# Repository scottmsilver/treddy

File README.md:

# Treddy

> A 2005 treadmill that listens when you talk to it.

A Raspberry Pi sits between the console and motor controller of a Precor 9.31 treadmill, intercepting the serial bus. It runs an AI coach (Gemini), voice control, a tablet UI, and a Bluetooth daemon that makes Zwift think it's a modern smart treadmill.

---

## Voice + AI Coach

- "Set speed to 5" or "give me a 20-minute hill workout" — Gemini controls the belt directly
- Voice works mid-run via Gemini Live (real-time, no wake word)
- Says "this is the hardest interval" or "you're faster than last time" because it can query your run history

## Apps

- **Android** (Kotlin + Compose): runs on a tablet mounted on the treadmill console
- **Web** (React + TypeScript): same features, any browser
- Workout library, run history, live elevation profile, calorie tracking

## Bluetooth

- Rust daemon makes the treadmill show up in Zwift, Peloton, QZ Fitness, and Apple Watch as a standard FTMS device
- Fitness apps can read speed/incline and write speed/incline commands back

## Heart Rate

- Connects to any Bluetooth heart rate strap
- HR shows in the UI and feeds into calorie calculations

---

## Architecture

```
┌───────────────────────────┬───────────────────────────┐
│  Web UI (React + Vite)    │  Android (Kotlin+Compose) │
├───────────────────────────┴───────────────────────────┤
│  REST / WebSocket / Gemini Live (voice)               │
├───────────────────────────────────────────────────────┤
│  server.py (FastAPI)                                  │
│  Sessions, programs, AI chat, workout query DB        │
├──────────────────┬──────────────┬─────────────────────┤
│  treadmill_io    │  ftms-daemon │  hrm-daemon         │
│  C++20, GPIO     │  Rust, BLE   │  Rust, BLE          │
│  serial, safety  │  FTMS        │  heart rate         │
└──────────────────┴──────────────┴─────────────────────┘
                         │
                    Precor 9.31
                  RS-485 serial bus
```

- **C++ binary** — reads/writes the serial bus, enforces safety (3-hour timeout, physical buttons always override software)
- **Python server** — FastAPI. All the logic: Gemini AI, workouts, sessions, run history
- **FTMS daemon** — Rust. Bluetooth for fitness apps
- **HRM daemon** — Rust. Connects to heart rate straps
- **Web + Android** — display layers. All decisions happen server-side.

Details: [CLAUDE.md](CLAUDE.md)

---

## The Hardware Story

> The serial protocol turned out to be plain ASCII text. We just had the polarity wrong and spent days decoding "binary" that was actually `[key:value]` pairs with every bit flipped.

[Full reverse engineering writeup →](HARDWARE.md)

---

## Quick Start

**Prerequisites (Pi):** `libpigpio-dev`, `g++`, Python 3 with `google-genai`, `fastapi`, `uvicorn`, `gpxpy`. Gemini API key in `.gemini_key`.

```bash
make                         # build C++ binary
sudo ./build/treadmill_io    # start GPIO daemon (must be root)
python3 python/server.py     # start web server → https://<pi>:8000
```

**Deploy to Pi:**
```bash
make deploy    # stages, rsyncs, builds on Pi, restarts all 4 services
```

**Local dev (no Pi needed):**
```bash
TREADMILL_MOCK=1 ./scripts/dev.sh    # Caddy + server + Vite HMR
```

API reference, tests, and dev docs: [CLAUDE.md](CLAUDE.md)

## License

MIT

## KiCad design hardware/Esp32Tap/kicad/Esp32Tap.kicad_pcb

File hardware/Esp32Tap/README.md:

# Esp32Tap Rev E

**Status: HOLD.** Do not submit fabrication, authorize substitutions, pay, or
connect an Emulate-capable build to a treadmill until the applicable vendor,
firmware, harness, and bench gates are closed.

Esp32Tap sits inline between the console and motor-controller serial cables of
a Precor 9.31. In Proxy mode a normally closed relay preserves the passive
console path. Emulate mode transfers that path to a hardware-gated ESP32-S3
transmitter. The treadmill safety key remains authoritative; this board is not
a certified functional-safety controller.

## Rev E architecture

- J1/J2 are both the identical Molex 44144-0003 (441440003, LCSC C585890)
  right-angle SMD 8P8C RJ45 jack, placed by standard top-side reflow (no
  through-hole RJ45, no wave or manual solder step), edge-mounted with the
  mating opening facing off a short board edge: J1 (CONSOLE) off the left
  edge, J2 (MOTOR) off the right edge, so the board reads console → motor left
  to right. There is no pigtail harness and no mechanical keying between
  console and motor; CONSOLE/MOTOR silkscreen is the only differentiator. The
  ESP32 module is fully on-board (no antenna overhang, no carrier panel).
- The treadmill cable's +8 V rails are the only board power input and pass
  directly between J1/J2. F1/D1 protect only the local branch.
- USB-C is native data and VBUS-presence sensing only. USB cannot energize the
  board or relay; programming needs current-limited serial +8 V bench power.
- K1 needs three things at once: `TREAD_OK`, `RELAY_CMD` static high, and
  `RELAY_PULSE` (U1 IO8) toggling. `TREAD_OK` also gates the motor TX buffer.
  `RELAY_GATE` (U6 output to U5 enable and the Q1 base) is unchanged; Q3, in
  series with Q1's emitter, is fed only by a charge pump from `RELAY_PULSE`.
  Calculated, not measured: the relay releases roughly 50-150 ms after
  toggling stops (not a guaranteed deadline), and one stray edge cannot turn
  Q3 on. The switch alone is not single-fault tolerant (C22 short, R34 open,
  C23 open or Q3 drain-source short each defeat it; each needs a second fault). The pulse
  firmware is implemented in `firmware/esp32_rs` but unproven on hardware (bd
  `precor-9_3x-4uv` stays open until bench proof): a 500 µs `esp_timer`
  callback toggles IO8 (1 kHz) only while the WDT-supervised serial engine keeps
  renewing a permission (every 5 ms pass; it expires 20 ms after the last
  renewal), so a hung safety loop stops the pulses within 20 ms. It is
  deliberately not LEDC/RMT/hardware PWM. Pulses are wanted only in
  EntryWaitGap, EntryWaitFeedback, Emulating and ExitWaitGap, so in Proxy a
  stuck `RELAY_GATE` still cannot energize K1.
- K1 uses one transfer pole and one armature-feedback pole; feedback does not
  prove transfer-contact continuity.
- U3 (USBLC6-2SC6) pin 5 is unconnected. Tied to the VBUS sense net it let the
  ESP32 D+ pull-up leak onto that net and could assert `VBUS_PRESENT_N` with
  no cable.
- D5-D7 are Nexperia PESD5V0S1BA,115 (LCSC C19224), 5 V standoff, because the
  treadmill serial line voltage has never been measured.
- R33 (1 MΩ, `TREAD_OK` to `UV_SENSE`) adds about 0.5 V of undervoltage
  hysteresis. Nominal UV is about 5.9 V falling and 6.4 V rising
  (calculated and simulated).
- SW1/SW2 (Alps SKRPACE010) pad numbering was corrected to rows (pad 1 = both
  top lands, pad 2 = both bottom lands). The old column numbering would have
  shorted EN and IO0 to GND through the switch body. Not yet proven on
  hardware.
- Three board-only fiducials FID1-FID3, and all stock footprints pinned in
  `tools/footprint_sources/stock` (`MANIFEST.json` sha256) so a KiCad library
  update can no longer make the board unreproducible.

## Package map

| Path | Purpose |
|---|---|
| `tools/design.py` | Electrical source of truth |
| `kicad/Esp32Tap.kicad_sch` | Generated typed schematic |
| `kicad/Esp32Tap.kicad_pcb` | Generated 95 × 58 mm four-layer PCB |
| `bom/BOM.csv` / `bom/CPL-positions.csv` | Exact assembly inputs |
| `kicad/Esp32Tap-gerbers.zip` | Deterministic 13-member fabrication archive |
| `kicad/models/` | Committed RJ45 jack 3D model (STEP + WRL, LCSC C585890) |
| `sim/` | Eight ngspice decks (one retired) and dual-engine assertion runner |
| `firmware/PLAN.md` | Production firmware and bench contract |
| `firmware/safety_model.py` | Host reference, not flashable firmware |
| `ORDERING.md` | HOLD-state vendor review procedure |
| `AI-HANDOFF.md` | Concise continuation brief |

Do not repair generated hardware or assembly outputs by hand.

## Locked board facts

| Item | Rev E value |
|---|---|
| Finished outline | 95.0 × 58.0 mm |
| Stack | Four layers; modeled 1.59 mm `JLC04161H-7628` |
| Board connectors | J1/J2 both Molex 44144-0003 (`441440003`, LCSC C585890), right-angle SMD 8P8C RJ45, unkeyed, standard top-side reflow; J1 (CONSOLE) on the left short edge, J2 (MOTOR) on the right short edge |
| BOM | 82 line items, 46 distinct LCSC parts, about $8.79 parts per board (generated `bom/BOM.csv`) |
| DRC | Fresh KiCad 10.0.5, all severities and schematic parity: 0 violations. The earlier committed `drc.rpt` claimed 0 while 10.0.5 reported 8 |
| Antenna | U1 fully on-board; 3.25/3.30 mm body margins. Keepout split: inner and bottom layers forbid tracks, vias and fills; the front layer forbids fills and vias and allows the U1 pad fan-out stubs. Fixture keepout emitted 0.30 mm inset |
| USB | F.Cu-only, zero signal vias, 0.2906 mm width / 0.2000 mm controlled edge gap |
| USB paths | D− A/B 55.9528786214/54.9528786214 mm; D+ A/B 55.8729617233/54.8729617233 mm |
| USB per-side skew | 0.0799168981 mm |
| 2 A PCB trace-union drop | 84.929 mV supply plus return (+8 V 17.313 mΩ, explicit-copper GND 25.151 mΩ; layer-aware copper model) |
| +8 via maximum | 0.827864 A; 7.482581 °C rise |
| GND-via envelope | Full 2.0 A in any via; 12.273573 °C and 1.600310 mW at 20 µm plating |

The GND return result is a conservative trace-only solve. The independent
full-current GND-via envelope covers omitted plane sharing; neither result
claims complete installed behavior.

## Reproduce

From repository root:

```bash
make -C hardware/Esp32Tap clean-check
make -C hardware/Esp32Tap check
git diff --check
```

The simulation runner executes twelve decks three times on host ngspice 42 and
pinned Docker ngspice 39. Passing proves only the declared models and artifact
parity. The Q3 liveness switch is simulated as a behavioral charge pump; the
times it reports are model outputs, not measurements.

## Bring-up sequence

1. Inspect identity, polarity, soldering, shorts, NC bypass, and TX isolation.
2. Apply current-limited +8 V at the documented RJ45 power contacts;
   verify VIN, +3V3, relay-off supply state, TREAD_OK, current, and temperature.
3. Establish a reviewed USB/treadmill bonding or isolation setup, then test
   VBUS presence, ROM/reset attach, enumeration, and unplug.
4. Use isolated serial fixtures for line loading, inverted idle, gap capture,
   relay transfer, feedback, and zero-frame ordering.
5. Complete the production firmware manifest and all `firmware/PLAN.md` gates.
6. Make first treadmill contact Proxy-only with relay energization compiled
   out. Emulate is a later, separately authorized test.

The exact unsupported harness claims are `RJ45_SINGLE_OPEN_2A`,
`MINIMUM_VIN`, `SOURCE_IMPEDANCE`, `AMBIENT_THERMAL`,
`TRANSIENT_RESPONSE`, `COMPLETE_INSTALLED_DROP`, `USB_RETURN_CURRENT`, `ESD`,
`RF`, and `SWITCHING_LOOP`.

## Known open items

- Live JLC review of the current archive/BOM/CPL/placement, 20 µm hole copper,
  J3 mechanical-stake reflow, and the enclosure quote remains open.
- 41 via drills still touch pasted SMD pads and were not rerouted. The order
  must select JLC's paid "Epoxy Filled & Capped" via covering (JLC states it
  is free only on 6+ layers; eligible holes up to 0.5 mm; price only from the
  quote tool). bd `precor-9_3x-ilf`.
- The board is 58 mm on one axis; JLC Standard PCBA needs 70 x 70 mm minimum
  plus rails and fiducials. The order needs JLC-added rails wide enough to reach
  70 mm (or a 2-up panel), with routed tabs kept away from C2, C7, F1, D1, D3
  and R5 near the bottom edge. Those parts were not moved. bd `precor-9_3x-idr`.
- CPL rotations are raw KiCad angles with no JLC correction table. Every
  polarized or multi-pin part must be checked in JLC's placement preview
  before paying. bd `precor-9_3x-f5y`.
- Treadmill serial line level and +8 V rail under load are unmeasured. bd
  `precor-9_3x-3pb`.
- `RELAY_PULSE` firmware is implemented, unproven on hardware (nothing has run
  on a board; QEMU cannot observe the charge pump; edge timing on the real pin
  under flash/network/BLE load needs a scope). bd `precor-9_3x-4uv`. Bench: scope
  Q1 base/emitter/collector when the pulses stop with `RELAY_GATE` high (BC817
  reverse VBE limit 5 V).
- Verified by eye: RJ45 footprint pad 1 (x = -4.45) matches Molex circuit 1,
  the leftmost contact land in the component-side layout of SD-44144-001 rev H9
  sheet 2. bd `precor-9_3x-192` is closed. A built board still has to confirm
  supply polarity and the pin-3/pin-6 taps.
- The buck input capacitor C3 was not moved closer to U2 (low-severity review
  note).
- `firmware/esp32_rs/partitions_esp32tap.csv` (nvs 24K, phy_init 4K, factory
  2 MB, storage LittleFS 1 MB) has not been verified against a real build.

The correct decision remains HOLD.

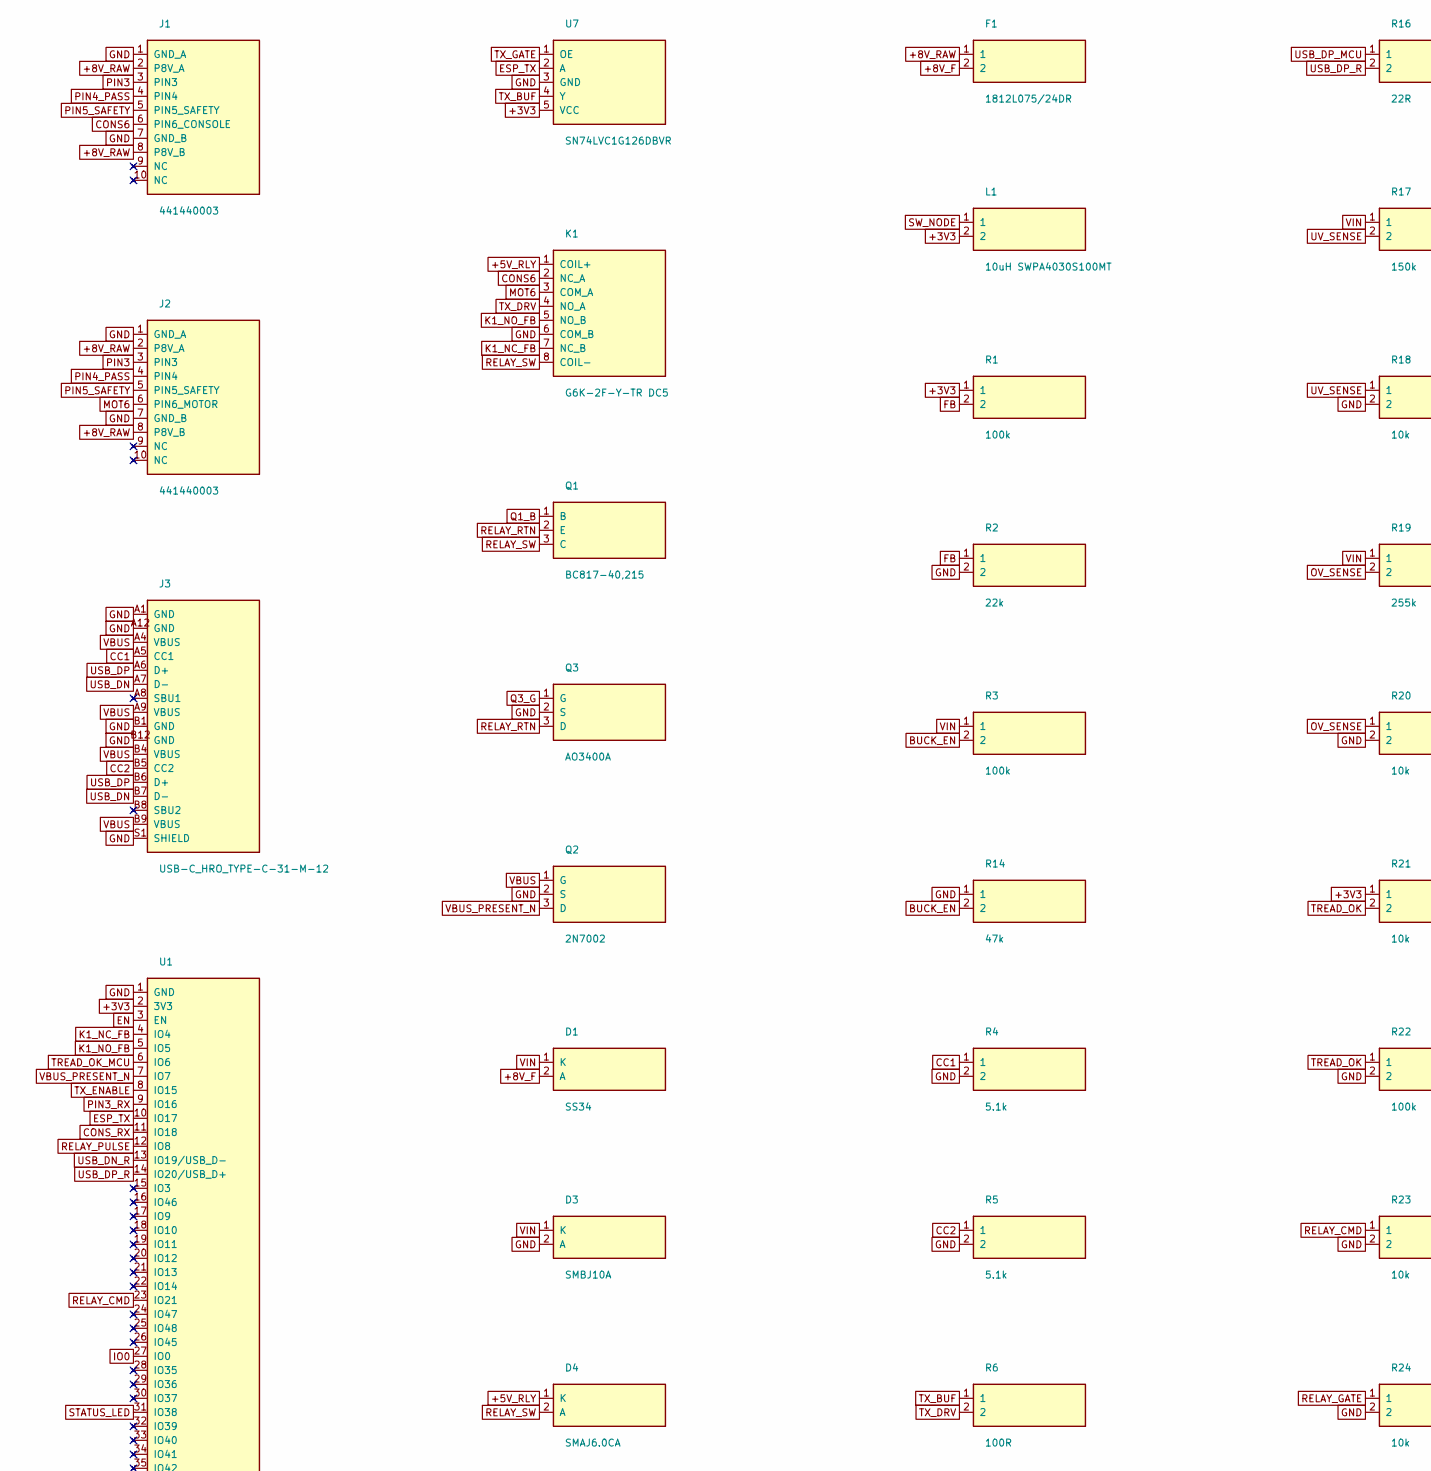
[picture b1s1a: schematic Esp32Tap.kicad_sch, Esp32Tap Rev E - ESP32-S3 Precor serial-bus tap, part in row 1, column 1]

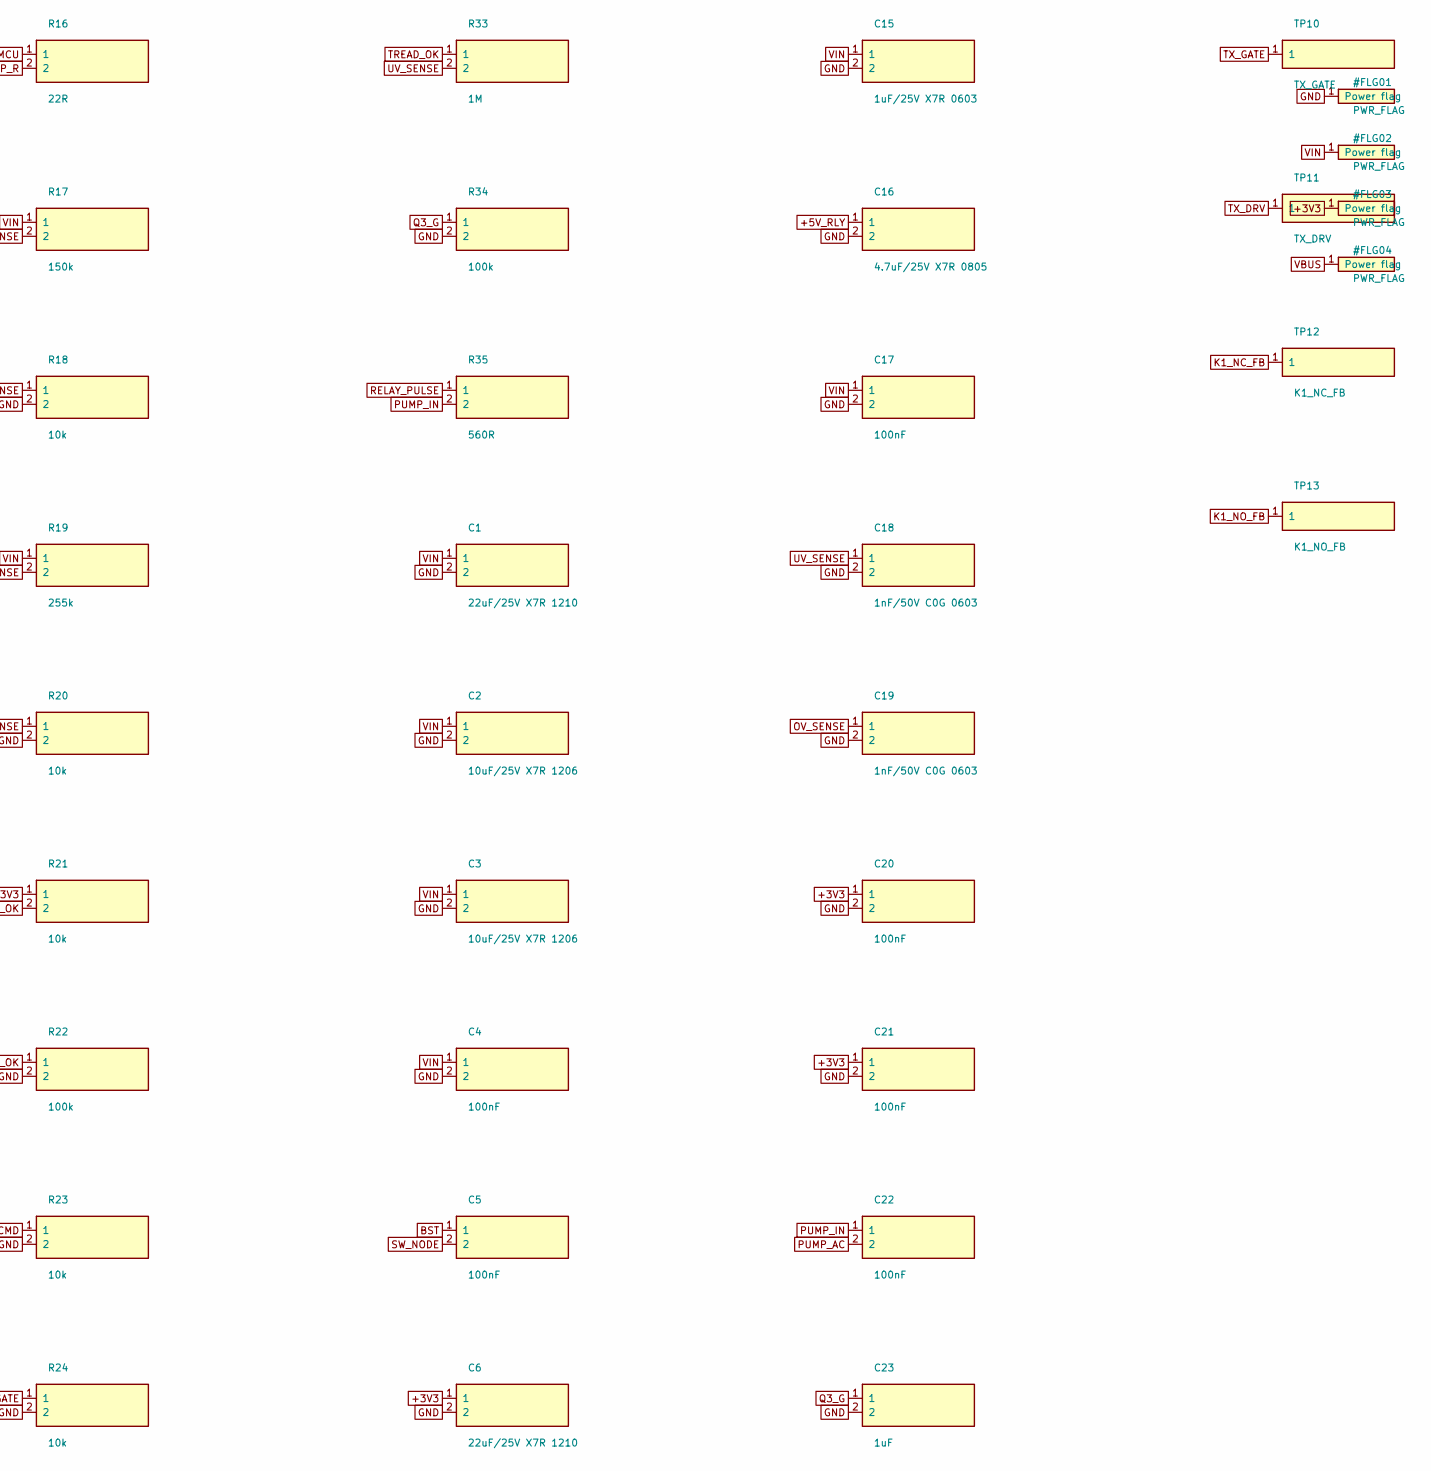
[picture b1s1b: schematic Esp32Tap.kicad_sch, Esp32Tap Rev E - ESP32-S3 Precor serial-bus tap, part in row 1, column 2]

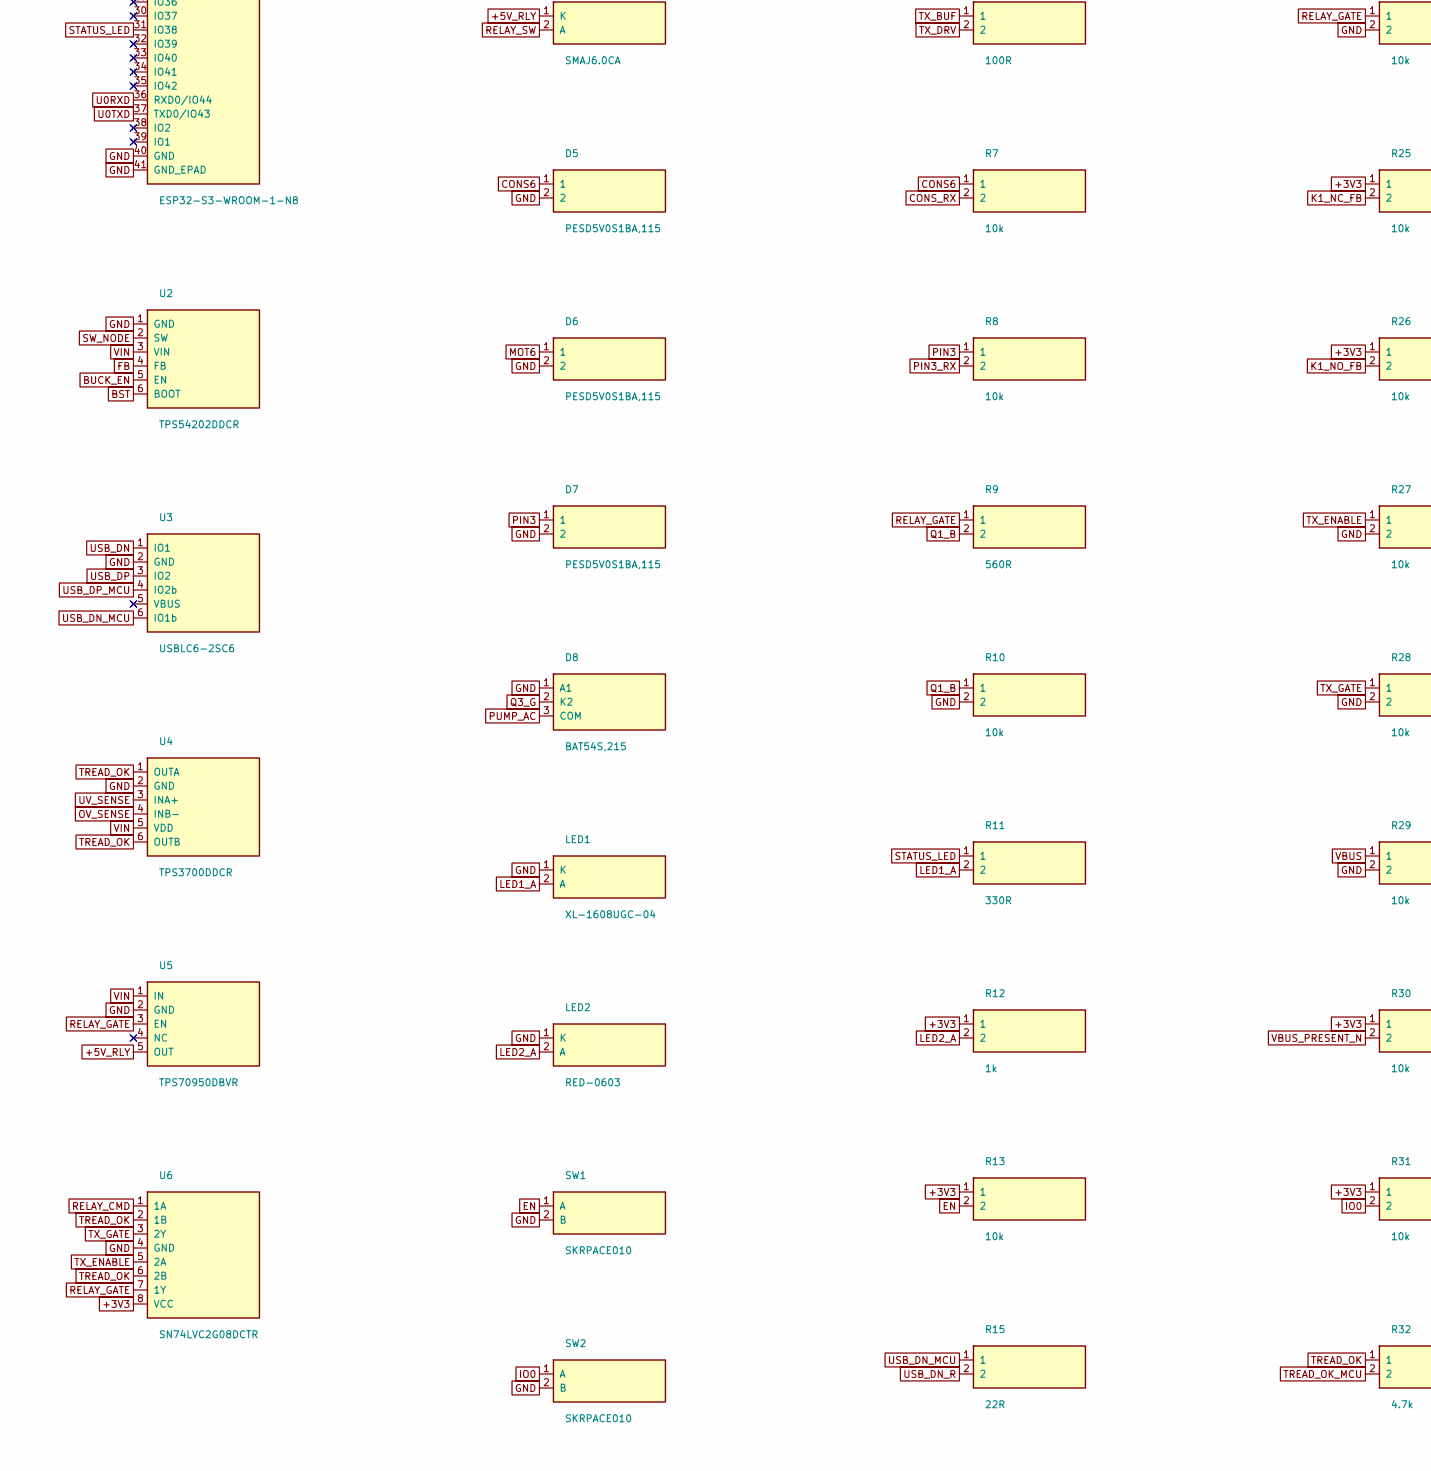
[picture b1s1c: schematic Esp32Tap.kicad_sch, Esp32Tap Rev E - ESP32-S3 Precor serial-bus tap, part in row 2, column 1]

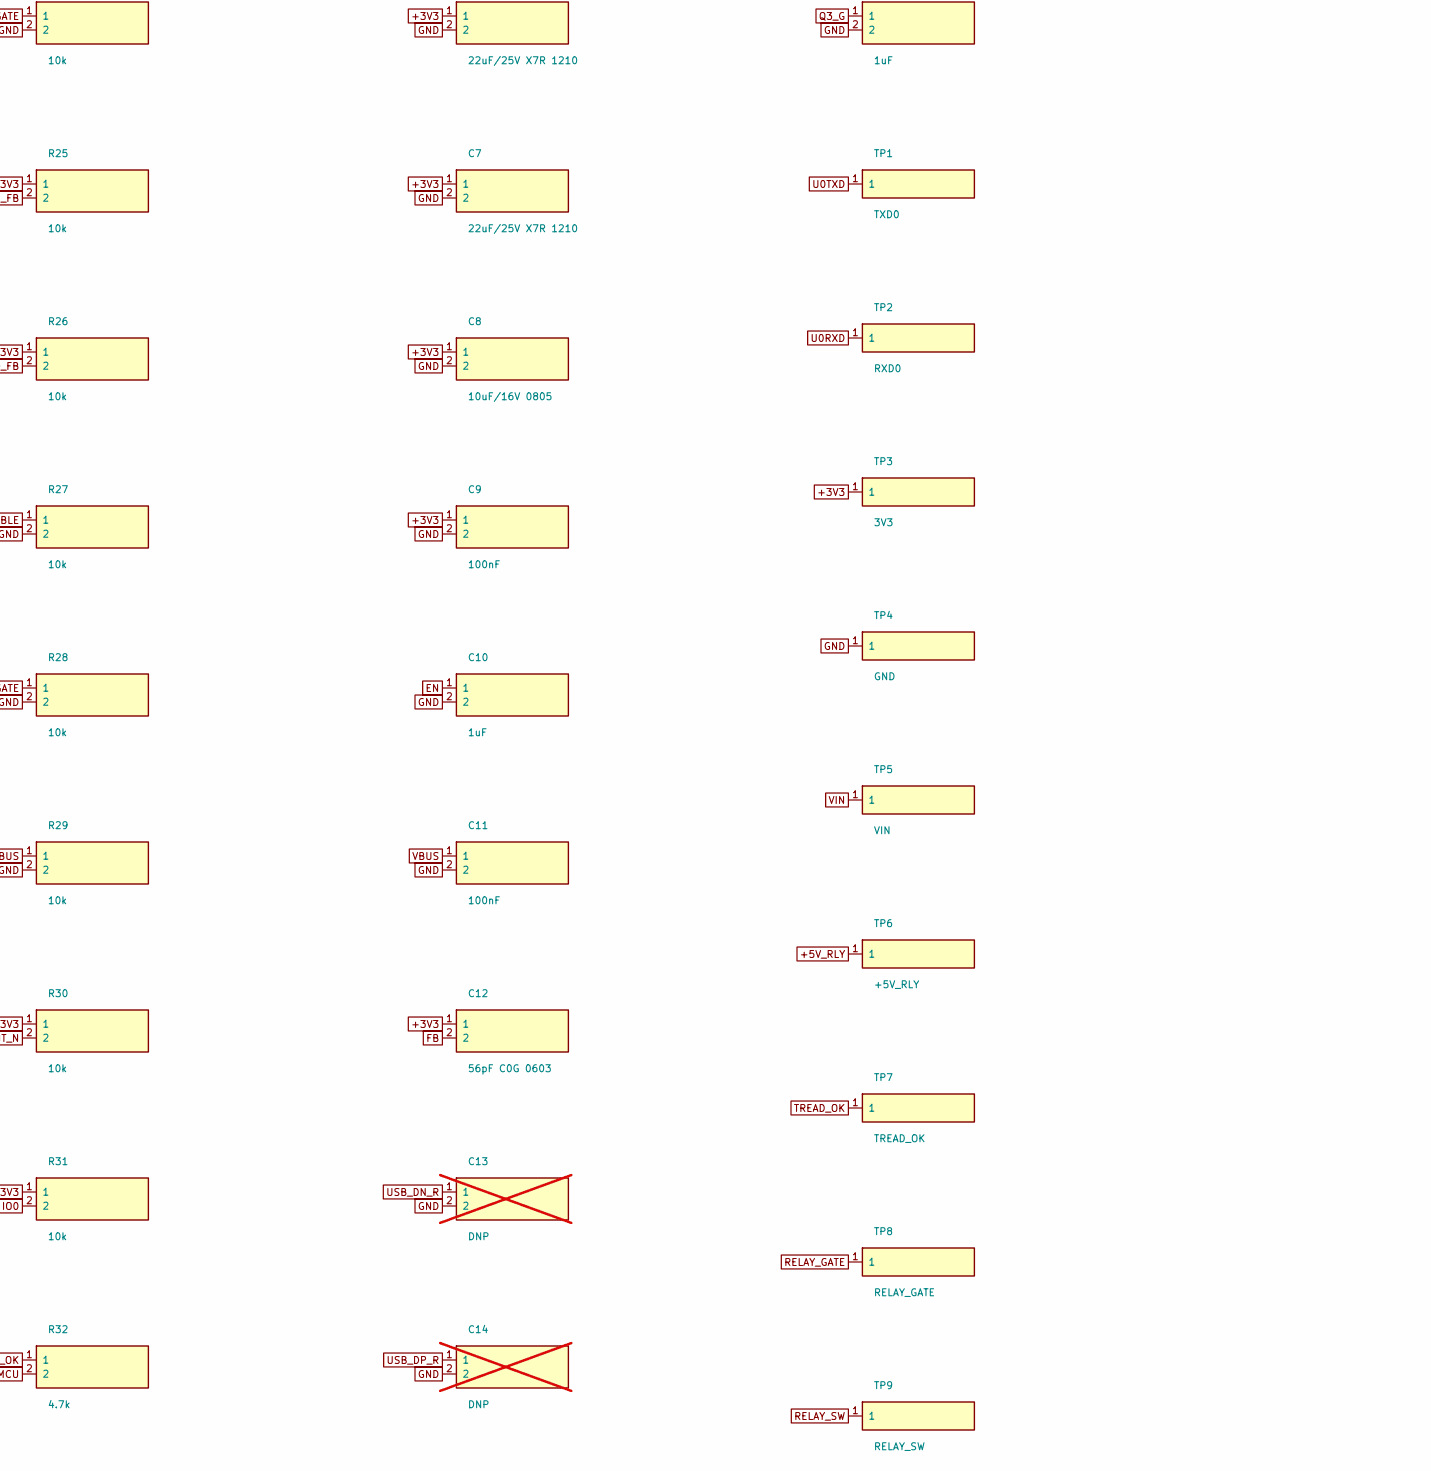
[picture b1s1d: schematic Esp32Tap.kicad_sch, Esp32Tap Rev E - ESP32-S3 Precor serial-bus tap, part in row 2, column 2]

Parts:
C1, C6, C7: 22uF/25V X7R 1210; C_1210_3225Metric; LCSC C2918511
C2, C3: 10uF/25V X7R 1206; C_1206_3216Metric; LCSC C14860
C4, C5, C9, C11, C17, C20, C21, C22: 100nF; C_0603_1608Metric; LCSC C14663
C8: 10uF/16V 0805; C_0805_2012Metric; LCSC C15850
C10, C23: 1uF; C_0603_1608Metric; LCSC C15849
C12: 56pF C0G 0603; C_0603_1608Metric; LCSC C39148
C13, C14: DNP; C_0603_1608Metric; JLC Class DNP; not fitted
C15: 1uF/25V X7R 0603; C_0603_1608Metric; LCSC C106858
C16: 4.7uF/25V X7R 0805; C_0805_2012Metric; LCSC C354262
C18, C19: 1nF/50V C0G 0603; C_0603_1608Metric; LCSC C342541
D1: SS34; D_SMA; LCSC C8678
D3: SMBJ10A; D_SMB; LCSC C151250
D4: SMAJ6.0CA; D_SMA; LCSC C80275
D5, D6, D7: PESD5V0S1BA,115; D_SOD-323; LCSC C19224
D8: BAT54S,215; SOT-23; LCSC C47546
F1: 1812L075/24DR; Fuse_1812_4532Metric; LCSC C207065
J1, J2: 441440003; RJ45-SMD_441440003; LCSC C585890
J3: USB-C_HRO_TYPE-C-31-M-12; USB_C_Receptacle_HRO_TYPE-C-31-M-12; LCSC C165948
K1: G6K-2F-Y-TR DC5; Relay_DPDT_Omron_G6K-2F-Y; LCSC C47190
L1: 10uH SWPA4030S100MT; L_Sunlord_SWPA4030S; LCSC C38117
LED1: XL-1608UGC-04; LED_0603_1608Metric; LCSC C965804
LED2: RED-0603; LED_0603_1608Metric; LCSC C2286
Q1: BC817-40,215; SOT-23; LCSC C52801
Q2: 2N7002; SOT-23; LCSC C8545
Q3: AO3400A; SOT-23; LCSC C20917
R1, R3, R22, R34: 100k; R_0603_1608Metric; LCSC C25803
R2: 22k; R_0603_1608Metric; LCSC C31850
R4, R5: 5.1k; R_0603_1608Metric; LCSC C23186
R6: 100R; R_0603_1608Metric; LCSC C22775
R7, R8, R10, R13, R18, R20, R21, R23, R24, R25, R26, R27, R28, R29, R30, R31: 10k; R_0603_1608Metric; LCSC C25804
R9, R35: 560R; R_0603_1608Metric; LCSC C23204
R11: 330R; R_0603_1608Metric; LCSC C23138
R12: 1k; R_0603_1608Metric; LCSC C21190
R14: 47k; R_0603_1608Metric; LCSC C25819
R15, R16: 22R; R_0603_1608Metric; LCSC C23345
R17: 150k; R_0603_1608Metric; LCSC C22807
R19: 255k; R_0603_1608Metric; LCSC C23354
R32: 4.7k; R_0603_1608Metric; LCSC C23162
R33: 1M; R_0603_1608Metric; LCSC C22935
SW1, SW2: SKRPACE010; SW_SPST_SKRPACE010; LCSC C139797
TP1: TXD0; TestPoint_Pad_1.5x1.5mm; JLC Class none
TP2: RXD0; TestPoint_Pad_1.5x1.5mm; JLC Class none
TP3: 3V3; TestPoint_Pad_1.5x1.5mm; JLC Class none
TP4: GND; TestPoint_Pad_1.5x1.5mm; JLC Class none
TP5: VIN; TestPoint_Pad_1.5x1.5mm; JLC Class none
TP6: +5V_RLY; TestPoint_Pad_1.5x1.5mm; JLC Class none
TP7: TREAD_OK; TestPoint_Pad_1.5x1.5mm; JLC Class none
TP8: RELAY_GATE; TestPoint_Pad_1.5x1.5mm; JLC Class none
TP9: RELAY_SW; TestPoint_Pad_1.5x1.5mm; JLC Class none
TP10: TX_GATE; TestPoint_Pad_1.5x1.5mm; JLC Class none
TP11: TX_DRV; TestPoint_Pad_1.5x1.5mm; JLC Class none
TP12: K1_NC_FB; TestPoint_Pad_1.5x1.5mm; JLC Class none
TP13: K1_NO_FB; TestPoint_Pad_1.5x1.5mm; JLC Class none
U1: ESP32-S3-WROOM-1-N8; ESP32-S3-WROOM-1; LCSC C2913198
U2: TPS54202DDCR; SOT-23-6; LCSC C191884
U3: USBLC6-2SC6; SOT-23-6; LCSC C7519
U4: TPS3700DDCR; SOT-23-6; LCSC C33002
U5: TPS70950DBVR; SOT-23-5; LCSC C96028
U6: SN74LVC2G08DCTR; SSOP-8_2.95x2.8mm_P0.65mm; LCSC C352973
U7: SN74LVC1G126DBVR; SOT-23-5; LCSC C7834

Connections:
+3V3: C6.1, C7.1, C8.1, C9.1, C12.1, C20.1, C21.1, L1.2, R1.1, R12.1, R13.1, R21.1, R25.1, R26.1, R30.1, R31.1, TP3.1, U1.2 (3V3), U6.8 (VCC), U7.5 (VCC)
+5V_RLY: C16.1, D4.1 (K), K1.1 (COIL+), TP6.1, U5.5 (OUT)
+8V_F: D1.2 (A), F1.2
+8V_RAW: F1.1, J1.2 (P8V_A), J1.8 (P8V_B), J2.2 (P8V_A), J2.8 (P8V_B)
BST: C5.1, U2.6 (BOOT)
BUCK_EN: R3.2, R14.2, U2.5 (EN)
CC1: J3.A5 (CC1), R4.1
CC2: J3.B5 (CC2), R5.1
CONS6: D5.1, J1.6 (PIN6_CONSOLE), K1.2 (NC_A), R7.1
CONS_RX: R7.2, U1.11 (IO18)
EN: C10.1, R13.2, SW1.1 (A), U1.3 (EN)
ESP_TX: U1.10 (IO17), U7.2 (A)
FB: C12.2, R1.2, R2.1, U2.4 (FB)
GND: C1.2, C2.2, C3.2, C4.2, C6.2, C7.2, C8.2, C9.2, C10.2, C11.2, C13.2, C14.2, C15.2, C16.2, C17.2, C18.2, C19.2, C20.2, C21.2, C23.2, D3.2 (A), D5.2, D6.2, D7.2, D8.1 (A1), J1.1 (GND_A), J1.7 (GND_B), J2.1 (GND_A), J2.7 (GND_B), J3.A1 (GND), J3.A12 (GND), J3.B1 (GND), J3.B12 (GND), J3.S1 (SHIELD), K1.6 (COM_B), LED1.1 (K), LED2.1 (K), Q2.2 (S), Q3.2 (S), R2.2, R4.2, R5.2, R10.2, R14.1, R18.2, R20.2, R22.2, R23.2, R24.2, R27.2, R28.2, R29.2, R34.2, SW1.2 (B), SW2.2 (B), TP4.1, U1.1 (GND), U1.40 (GND), U1.41 (GND_EPAD), U2.1 (GND), U3.2 (GND), U4.2 (GND), U5.2 (GND), U6.4 (GND), U7.3 (GND)
IO0: R31.2, SW2.1 (A), U1.27 (IO0)
K1_NC_FB: K1.7 (NC_B), R25.2, TP12.1, U1.4 (IO4)
K1_NO_FB: K1.5 (NO_B), R26.2, TP13.1, U1.5 (IO5)
LED1_A: LED1.2 (A), R11.2
LED2_A: LED2.2 (A), R12.2
MOT6: D6.1, J2.6 (PIN6_MOTOR), K1.3 (COM_A)
OV_SENSE: C19.1, R19.2, R20.1, U4.4 (INB-)
PIN3: D7.1, J1.3 (PIN3), J2.3 (PIN3), R8.1
PIN3_RX: R8.2, U1.9 (IO16)
PIN4_PASS: J1.4 (PIN4), J2.4 (PIN4)
PIN5_SAFETY: J1.5 (PIN5_SAFETY), J2.5 (PIN5_SAFETY)
PUMP_AC: C22.2, D8.3 (COM)
PUMP_IN: C22.1, R35.2
Q1_B: Q1.1 (B), R9.2, R10.1
Q3_G: C23.1, D8.2 (K2), Q3.1 (G), R34.1
RELAY_CMD: R23.1, U1.23 (IO21), U6.1 (1A)
RELAY_GATE: R9.1, R24.1, TP8.1, U5.3 (EN), U6.7 (1Y)
RELAY_PULSE: R35.1, U1.12 (IO8)
RELAY_RTN: Q1.2 (E), Q3.3 (D)
RELAY_SW: D4.2 (A), K1.8 (COIL-), Q1.3 (C), TP9.1
STATUS_LED: R11.1, U1.31 (IO38)
SW_NODE: C5.2, L1.1, U2.2 (SW)
TREAD_OK: R21.2, R22.1, R32.1, R33.1, TP7.1, U4.1 (OUTA), U4.6 (OUTB), U6.2 (1B), U6.6 (2B)
TREAD_OK_MCU: R32.2, U1.6 (IO6)
TX_BUF: R6.1, U7.4 (Y)
TX_DRV: K1.4 (NO_A), R6.2, TP11.1
TX_ENABLE: R27.1, U1.8 (IO15), U6.5 (2A)
TX_GATE: R28.1, TP10.1, U6.3 (2Y), U7.1 (OE)
U0RXD: TP2.1, U1.36 (RXD0/IO44)
U0TXD: TP1.1, U1.37 (TXD0/IO43)
USB_DN: J3.A7 (D-), J3.B7 (D-), U3.1 (IO1)
USB_DN_MCU: R15.1, U3.6 (IO1b)
USB_DN_R: C13.1, R15.2, U1.13 (IO19/USB_D-)
USB_DP: J3.A6 (D+), J3.B6 (D+), U3.3 (IO2)
USB_DP_MCU: R16.1, U3.4 (IO2b)
USB_DP_R: C14.1, R16.2, U1.14 (IO20/USB_D+)
UV_SENSE: C18.1, R17.2, R18.1, R33.2, U4.3 (INA+)
VBUS: C11.1, J3.A4 (VBUS), J3.A9 (VBUS), J3.B4 (VBUS), J3.B9 (VBUS), Q2.1 (G), R29.1
VBUS_PRESENT_N: Q2.3 (D), R30.2, U1.7 (IO7)
VIN: C1.1, C2.1, C3.1, C4.1, C15.1, C17.1, D1.1 (K), D3.1 (K), R3.1, R17.1, R19.1, TP5.1, U2.3 (VIN), U4.5 (VDD), U5.1 (IN)

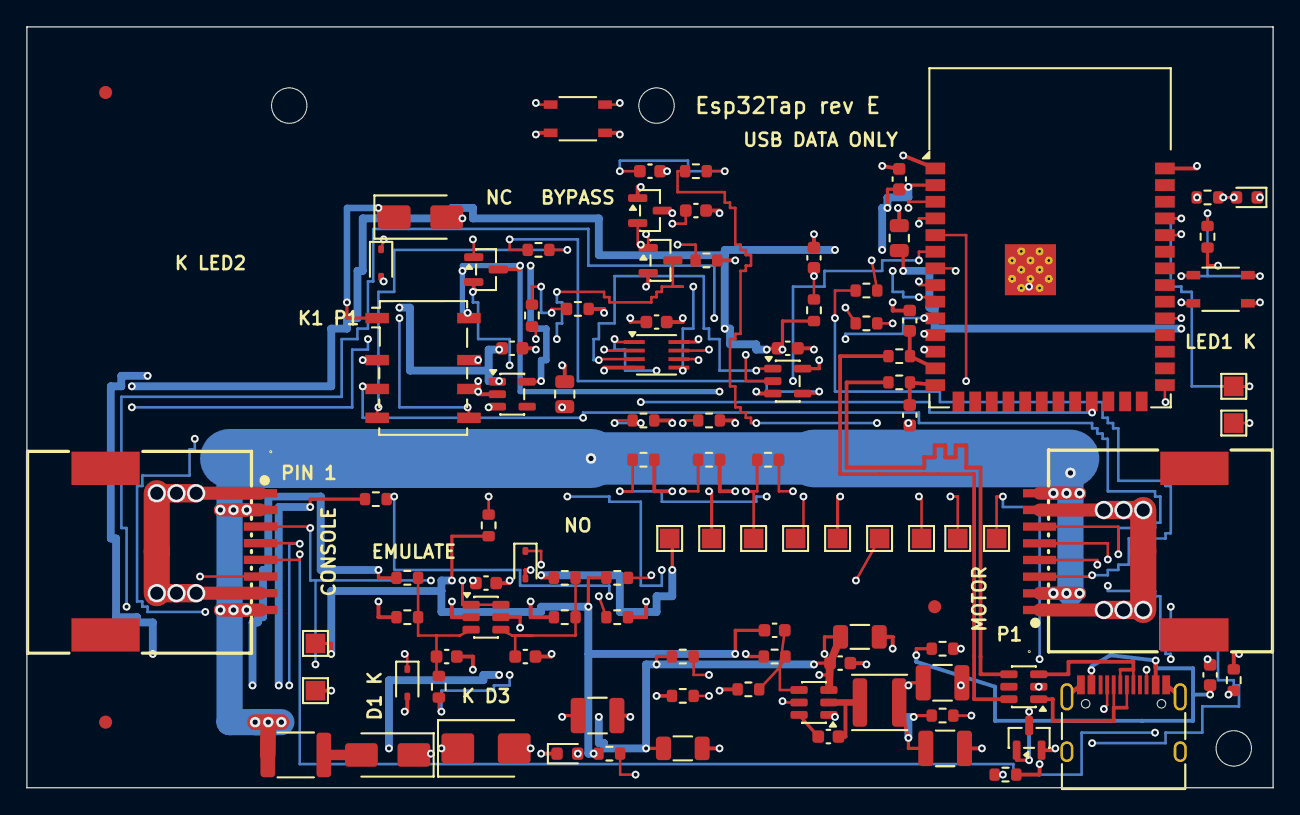
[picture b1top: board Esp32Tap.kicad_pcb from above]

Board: 4 copper layers, 95.0 x 58.0 mm, 104 parts (0 on the bottom side), 54 nets.

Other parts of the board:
FID1, FID2, FID3: Fiducial; Fiducial_1mm_Mask2mm
MH1, MH2, MH3: M2.5; MountingHole_2.7mm_M2.5

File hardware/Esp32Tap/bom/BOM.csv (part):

Comment,Designator,Footprint,LCSC Part #,JLC class,Qty,Unit cost (USD),Ext cost (USD),Description
441440003,J1,RJ45-SMD_441440003,C585890,Extended,1,0.350,0.350,Molex 441440003 unshielded right-angle SMD 8P8C RJ45 jack — console interface; edge-mounted with the mating opening facing off the board edge so a standard RJ45 plug reaches through the enclosure wall aperture; pads 9/10 are mechanical-only (NC).
441440003,J2,RJ45-SMD_441440003,C585890,Extended,1,0.350,0.350,Molex 441440003 unshielded right-angle SMD 8P8C RJ45 jack — motor interface; edge-mounted with the mating opening facing off the board edge so a standard RJ45 plug reaches through the enclosure wall aperture; pads 9/10 are mechanical-only (NC).
USB-C_HRO_TYPE-C-31-M-12,J3,USB_C_Receptacle_HRO_TYPE-C-31-M-12,C165948,Extended,1,0.160,0.160,"USB-C receptacle, 16-pin, USB2.0 — native USB flash/JTAG/console"
ESP32-S3-WROOM-1-N8,U1,ESP32-S3-WROOM-1,C2913198,Extended,1,3.200,3.200,"ESP32-S3 module, 8MB flash, PCB antenna (N8R2 C2913204 is a drop-in PSRAM upgrade — same footprint; re-quote at order time)"
TPS54202DDCR,U2,SOT-23-6,C191884,Extended,1,0.350,0.350,"Buck converter 4.5-28V in, 2A, 500kHz — 8V rail to 3.3V"
USBLC6-2SC6,U3,SOT-23-6,C7519,Extended,1,0.200,0.200,USB ESD protection array
TPS3700DDCR,U4,SOT-23-6,C33002,Extended,1,0.780,0.780,Window voltage supervisor with open-drain outputs
TPS70950DBVR,U5,SOT-23-5,C96028,Extended,1,0.420,0.420,5V 150mA LDO with enable for relay-coil supply
SN74LVC2G08DCTR,U6,SSOP-8_2.95x2.8mm_P0.65mm,C352973,Extended,1,0.160,0.160,Dual two-input AND gate with partial-power-down support
SN74LVC1G126DBVR,U7,SOT-23-5,C7834,Extended,1,0.110,0.110,Single tri-state buffer with partial-power-down support
G6K-2F-Y-TR DC5,K1,Relay_DPDT_Omron_G6K-2F-Y,C47190,Extended,1,1.500,1.500,"DPDT signal relay, 5VDC coil, SMD — pole A provides fail-safe serial bypass and pole B provides dry-contact armature feedback"
"BC817-40,215",Q1,SOT-23,C52801,Extended,1,0.030,0.030,45V NPN relay coil driver
AO3400A,Q3,SOT-23,C20917,Basic,1,0.030,0.030,"30V logic-level N-MOSFET (Vgs(th) 0.65-1.45V) in series with Q1's emitter: the relay liveness switch. Its gate is fed only by the RELAY_PULSE charge pump, so the coil return path exists only while firmware keeps toggling that pin (1 kHz square wave or faster: the gate then sits near 2.5 V, the AO3400A's specified drive level)"
2N7002,Q2,SOT-23,C8545,Basic,1,0.020,0.020,"N-channel MOSFET, active-low VBUS-present detector"
SS34,D1,D_SMA,C8678,Basic,1,0.050,0.050,Series Schottky providing reverse-polarity protection for local VIN
SMBJ10A,D3,D_SMB,C151250,Extended,1,0.050,0.050,"TVS, Littelfuse SMBJ10A — protected-VIN transient clamp"
SMAJ6.0CA,D4,D_SMA,C80275,Extended,1,0.050,0.050,Bidirectional TVS directly across the relay coil for fast release
"PESD5V0S1BA,115",D5,D_SOD-323,C19224,Extended,1,0.050,0.050,"Bidirectional ESD clamp to GND (NOT rail-referenced), console pin-6 line. 5V standoff: the treadmill bus level has never been measured, and this clamp sits on the console-to-motor path even in unpowered bypass, so it must stay inert on a 5V bus as well as a 3.3V one (Nexperia PESD5V0S1BA, 35pF)"
"PESD5V0S1BA,115",D6,D_SOD-323,C19224,Extended,1,0.050,0.050,"Bidirectional 5V-standoff ESD clamp, motor pin-6 line"
"PESD5V0S1BA,115",D7,D_SOD-323,C19224,Extended,1,0.050,0.050,"Bidirectional 5V-standoff ESD clamp, pin-3 tap line"
"BAT54S,215",D8,SOT-23,C47546,Extended,1,0.030,0.030,"Series Schottky pair: relay liveness charge-pump rectifier (pin 1 anode to GND, pin 3 common to the pump capacitor, pin 2 cathode to the Q3 gate)"
XL-1608UGC-04,LED1,LED_0603_1608Metric,C965804,Extended,1,0.005,0.005,"Status LED green (GPIO38; XL-1608UGC-04, 5.2M stock at validation 2026-07-23; replaces C72043 stock=6)"
RED-0603,LED2,LED_0603_1608Metric,C2286,Basic,1,0.020,0.020,3V3 power LED
SKRPACE010,SW1,SW_SPST_SKRPACE010,C139797,Extended,1,0.060,0.060,ALPSALPINE SKRPACE010 reel SMD tactile switch — reset (EN); PROVISIONAL_REQUIRES_LIVE_BOM_CPL_PROOF
SKRPACE010,SW2,SW_SPST_SKRPACE010,C139797,Extended,1,0.060,0.060,ALPSALPINE SKRPACE010 reel SMD tactile switch — boot (IO0); PROVISIONAL_REQUIRES_LIVE_BOM_CPL_PROOF
1812L075/24DR,F1,Fuse_1812_4532Metric,C207065,Extended,1,0.100,0.100,"Resettable fuse on the local 8V branch, 0.75A hold, 24V maximum"
10uH SWPA4030S100MT,L1,L_Sunlord_SWPA4030S,C38117,Extended,1,0.070,0.070,"Buck inductor, 4x4mm shielded, Isat 2.4A (sized for ~0.6A peaks)"
100k,R1,R_0603_1608Metric,C25803,Basic,1,0.002,0.002,Buck FB divider top (VFB 0.596V -> 3.30V with 22k)
22k,R2,R_0603_1608Metric,C31850,Basic,1,0.002,0.002,Buck FB divider bottom
100k,R3,R_0603_1608Metric,C25803,Basic,1,0.002,0.002,Buck EN divider top from protected VIN (with R14 47k bottom: EN remains above the enable threshold at the approved VIN window and below the TPS54202 7V EN absolute maximum)
47k,R14,R_0603_1608Metric,C25819,Basic,1,0.002,0.002,Buck EN divider bottom — keeps EN below the 7V abs-max at treadmill VIN (a bare pull-up would float EN to ~7.6V)
5.1k,R4,R_0603_1608Metric,C23186,Basic,1,0.002,0.002,USB-C CC1 sink resistor
5.1k,R5,R_0603_1608Metric,C23186,Basic,1,0.002,0.002,USB-C CC2 sink resistor
100R,R6,R_0603_1608Metric,C22775,Basic,1,0.002,0.002,"Motor-pin6 TX series resistor (drive path; isolated by relay when unpowered, so 100R is safe here)"
10k,R7,R_0603_1608Metric,C25804,Basic,1,0.002,0.002,Console-pin6 RX tap series resistor — limits unpowered GPIO-clamp back-feed
10k,R8,R_0603_1608Metric,C25804,Basic,1,0.002,0.002,Pin-3 tap series resistor — limits unpowered GPIO-clamp back-feed
560R,R9,R_0603_1608Metric,C23204,Basic,1,0.002,0.002,Relay driver base resistor (forced beta <= 10 at conservative drive)
10k,R10,R_0603_1608Metric,C25804,Basic,1,0.002,0.002,Relay driver base pull-down (relay stays off during boot/reset)
330R,R11,R_0603_1608Metric,C23138,Basic,1,0.002,0.002,Status LED resistor (330R: 1.51mA typ through LED1 — validation fix F1; 1k gave a sub-visible 0.6mA)
1k,R12,R_0603_1608Metric,C21190,Basic,1,0.002,0.002,Power LED resistor (1k for a clearly visible power light; was 2k at 0.78mA)
10k,R13,R_0603_1608Metric,C25804,Basic,1,0.002,0.002,EN (reset) pull-up
22R,R15,R_0603_1608Metric,C23345,Basic,1,0.002,0.002,USB D- series termination
22R,R16,R_0603_1608Metric,C23345,Basic,1,0.002,0.002,USB D+ series termination
150k,R17,R_0603_1608Metric,C22807,Basic,1,0.002,0.002,"Undervoltage-sense divider top, 1%"
10k,R18,R_0603_1608Metric,C25804,Basic,1,0.002,0.002,"Undervoltage-sense divider bottom, 1%"
255k,R19,R_0603_1608Metric,C23354,Extended,1,0.002,0.002,"Overvoltage-sense divider top, 1%"
10k,R20,R_0603_1608Metric,C25804,Basic,1,0.002,0.002,"Overvoltage-sense divider bottom, 1%"
10k,R21,R_0603_1608Metric,C25804,Basic,1,0.002,0.002,TREAD_OK pull-up
100k,R22,R_0603_1608Metric,C25803,Basic,1,0.002,0.002,TREAD_OK power-off pull-down
10k,R23,R_0603_1608Metric,C25804,Basic,1,0.002,0.002,RELAY_CMD pull-down
10k,R24,R_0603_1608Metric,C25804,Basic,1,0.002,0.002,RELAY_GATE pull-down at U5 enable
10k,R25,R_0603_1608Metric,C25804,Basic,1,0.002,0.002,Relay normally-closed feedback pull-up
10k,R26,R_0603_1608Metric,C25804,Basic,1,0.002,0.002,Relay normally-open feedback pull-up
10k,R27,R_0603_1608Metric,C25804,Basic,1,0.002,0.002,TX_ENABLE pull-down
10k,R28,R_0603_1608Metric,C25804,Basic,1,0.002,0.002,TX_GATE pull-down at U7 output enable
10k,R29,R_0603_1608Metric,C25804,Basic,1,0.002,0.002,USB VBUS discharge
10k,R30,R_0603_1608Metric,C25804,Basic,1,0.002,0.002,VBUS_PRESENT_N pull-up
10k,R31,R_0603_1608Metric,C25804,Basic,1,0.002,0.002,GPIO0 boot pull-up
4.7k,R32,R_0603_1608Metric,C23162,Basic,1,0.002,0.002,TREAD_OK→IO6 series isolation: keeps a misconfigured GPIO from overriding the U4 window or contending with its open-drain (review finding B2)
1M,R33,R_0603_1608Metric,C22935,Basic,1,0.002,0.002,Undervoltage hysteresis: positive feedback from TREAD_OK to UV_SENSE adds about 0.45V of VIN-referred hysteresis so load bursts near the UV threshold cannot chatter the relay
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
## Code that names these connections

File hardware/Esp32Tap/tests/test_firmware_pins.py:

"""The Rust firmware's pin table must agree with the board.

``firmware/esp32_rs/esp32tap/src/pins.rs`` says it is checked against
``design.py``, but the only pin checker the firmware build runs reads the
legacy C++ ``pins.hpp``. This test is the check for the Rust table: every
``K_<NET>`` constant must name a net with exactly one U1 pad, carry that pad's
GPIO number, and have the right direction in ``design.PIN_TYPES``.
"""

from __future__ import annotations

import re
import sys
from pathlib import Path

ROOT = Path(__file__).resolve().parents[1]
sys.path.insert(0, str(ROOT / "tools"))

import design  # noqa: E402

PINS_RS = ROOT / "firmware" / "esp32_rs" / "esp32tap" / "src" / "pins.rs"
OUTPUT_NETS = {"RELAY_CMD", "RELAY_PULSE", "TX_ENABLE", "ESP_TX", "STATUS_LED"}
INPUT_NETS = {"TREAD_OK_MCU", "K1_NC_FB", "K1_NO_FB", "VBUS_PRESENT_N", "CONS_RX", "PIN3_RX"}


def rust_pins() -> dict[str, int]:
    text = PINS_RS.read_text(encoding="utf-8")
    return {name: int(value) for name, value in re.findall(r"pub const K_(\w+): u32 = (\d+);", text)}


def board_gpio(net: str) -> tuple[str, int]:
    pads = [pad for ref, pad in design.NETS[net] if ref == "U1"]
    assert len(pads) == 1, f"net {net} has {len(pads)} U1 pads"
    match = re.search(r"IO(\d+)", design.COMPONENTS["U1"][7][pads[0]])
    assert match, f"U1 pad {pads[0]} is not a GPIO"
    return pads[0], int(match.group(1))


def test_every_rust_pin_constant_matches_the_board() -> None:
    pins = rust_pins()
    assert set(pins) == OUTPUT_NETS | INPUT_NETS
    for net, gpio in pins.items():
        pad, expected = board_gpio(net)
        assert gpio == expected, f"K_{net} = {gpio}, but the board routes {net} to U1 pad {pad} = GPIO{expected}"
        direction = design.PIN_TYPES[("U1", pad)]
        assert direction == ("output" if net in OUTPUT_NETS else "input"), f"{net}: U1 pad {pad} is {direction}"


def test_relay_pulse_is_gpio8_and_reaches_only_the_pump_resistor() -> None:
    assert rust_pins()["RELAY_PULSE"] == 8
    assert sorted(design.NETS["RELAY_PULSE"]) == [("R35", "1"), ("U1", "12")]


def test_no_safety_output_is_a_strapping_pin() -> None:
    strapping = {0, 3, 45, 46}
    for net in OUTPUT_NETS:
        assert rust_pins()[net] not in strapping, f"{net} is on a strapping pin"

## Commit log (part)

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2026-02-19 Update README with connection details and pin info
    Removed a diagram representation of connections and updated the note about pin assignments.
2026-04-02 chore: ignore local worktrees
